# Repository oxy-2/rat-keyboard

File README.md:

# rat keyboard
i made a keyboard with a cute little screen that can show rotating text, like "i love rats <3"

so this is my hackpad aka macropad with the little hackclub program, here you can see the guide  
https://hackpad.hackclub.com/

however i have done mine with onshape instead of fusion as i have a general dislike for fusion from when i tried making pcbs with it.

so this project was done with the assistance of ai in designing and things i didn't know, obviously though i modeled out the mount  also little note the exported files are stl, step files wont export
and made the pcbs myself with kicad, and the firmware is the same as the guide, its just qmk.

as for the components they are all given by hackclub for this so i will not list a vendor or price but here  is a simple table with the components and amount needed for this project:

| Component                 | Quantity |
| ------------------------- | -------- |
| MX style switches         | 4x       |
| Seeed XIAO RP2040         | 1x       |
| 1 EC11E Rotary encoder    | 1x       |
| 0.91 inch OLED display    | 1x       |
| white blank DSA keycaps   | 4x       |
| M3x16mm screws            | 5x       |
| M3x5mx4mm heatset inserts | 5x       |

but yeah so the build will of course need its pcbs, the pcbs fit the under the max size of the hackpad guide, so it should be cheap enough as just a two layer under 100x100 mm pcb, also the case should fit, when i made the case i decided id do the pcb with some extra money from me or sum to make it white and maybe maybe maybe ENIG, but yeah thats for me to get after i make this but yeah so i wanted a pretty pcb and to show it off so the case is a mount to hold it up and its just open to air, i personally like the ig exposed style, anyways here are pictures of the pcb.

front:

back:

oh and heres a pic from cad:

shcematic:

pcb in kicad:

but yeah so its got 4 keys, a rotary encoder with a switch and a oled, on the oled it has wrapping text that spins and its correlated to the system volume which the knob can change and a press down is a volume mute and unmute, rn the text is "i love rats <3" but if you don't like it or want sum else you can easily change it in the firmware.
oh yeah btw the onshape document is set to public so you can check it out at the link [here](https://cad.onshape.com/documents/287181afc6cc633650b51987/w/7a5487d578a409bebd3abe5a/e/d938dcab35d572d75bd97ac9?renderMode=0&uiState=6aafc34289e7540c48d2f54f)
thank you for your time <3

-oxy

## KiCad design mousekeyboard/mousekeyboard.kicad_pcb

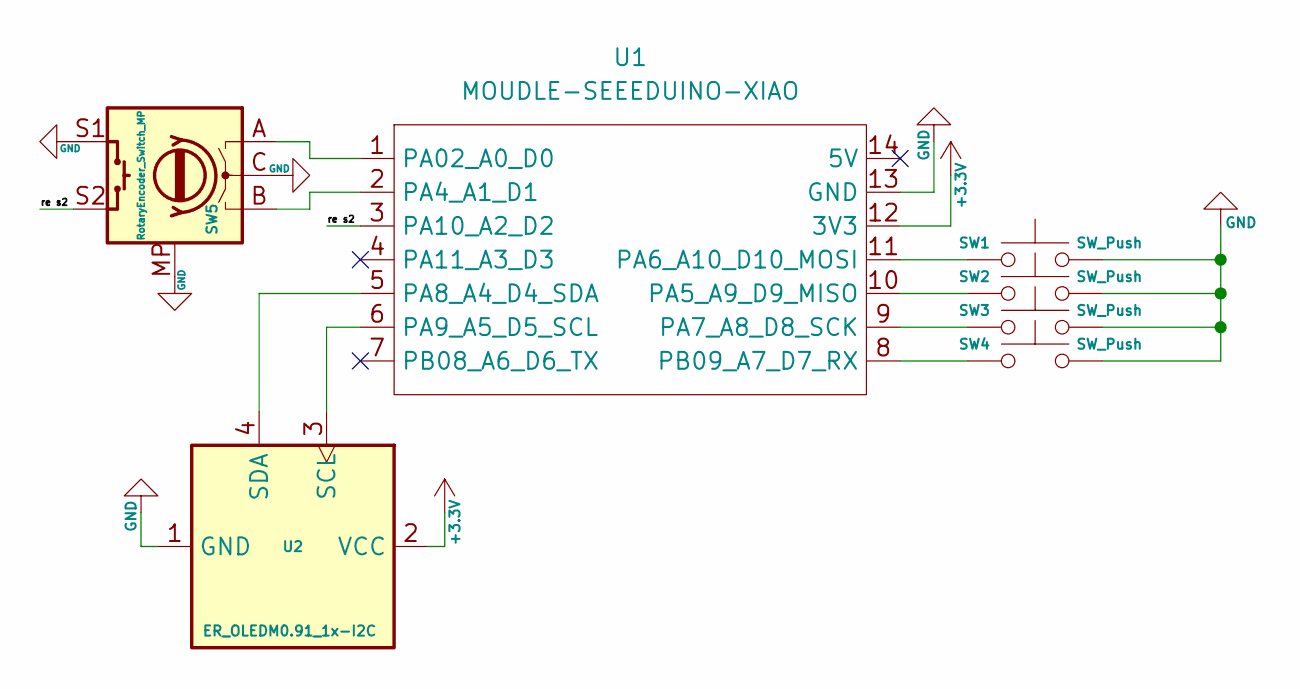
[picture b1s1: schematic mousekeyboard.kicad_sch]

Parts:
SW1, SW2, SW3, SW4: SW_Push; SW_Cherry_MX_1.00u_PCB
SW5: RotaryEncoder_Switch_MP; RotaryEncoder_Alps_EC11E-Switch_Vertical_H20mm
U1: MOUDLE-SEEEDUINO-XIAO; XIAO-Generic-Hybrid-14P-2.54-21X17.8MM
U2: ER_OLEDM0.91_1x-I2C

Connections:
+3.3V: U1.12 (3V3), U2.2 (VCC)
/re s2: SW5.S2, U1.3 (PA10_A2_D2)
GND: SW1.2, SW2.2, SW3.2, SW4.2, SW5.C, SW5.MP, SW5.S1, U1.13 (GND), U2.1 (GND)
unnamed: SW5.A, U1.1 (PA02_A0_D0)
unnamed: SW5.B, U1.2 (PA4_A1_D1)
unnamed: SW2.1, U1.10 (PA5_A9_D9_MISO)
unnamed: SW1.1, U1.11 (PA6_A10_D10_MOSI)
unnamed: SW3.1, U1.9 (PA7_A8_D8_SCK)
unnamed: U1.5 (PA8_A4_D4_SDA), U2.4 (SDA)
unnamed: U1.6 (PA9_A5_D5_SCL), U2.3 (SCL)
unnamed: SW4.1, U1.8 (PB09_A7_D7_RX)

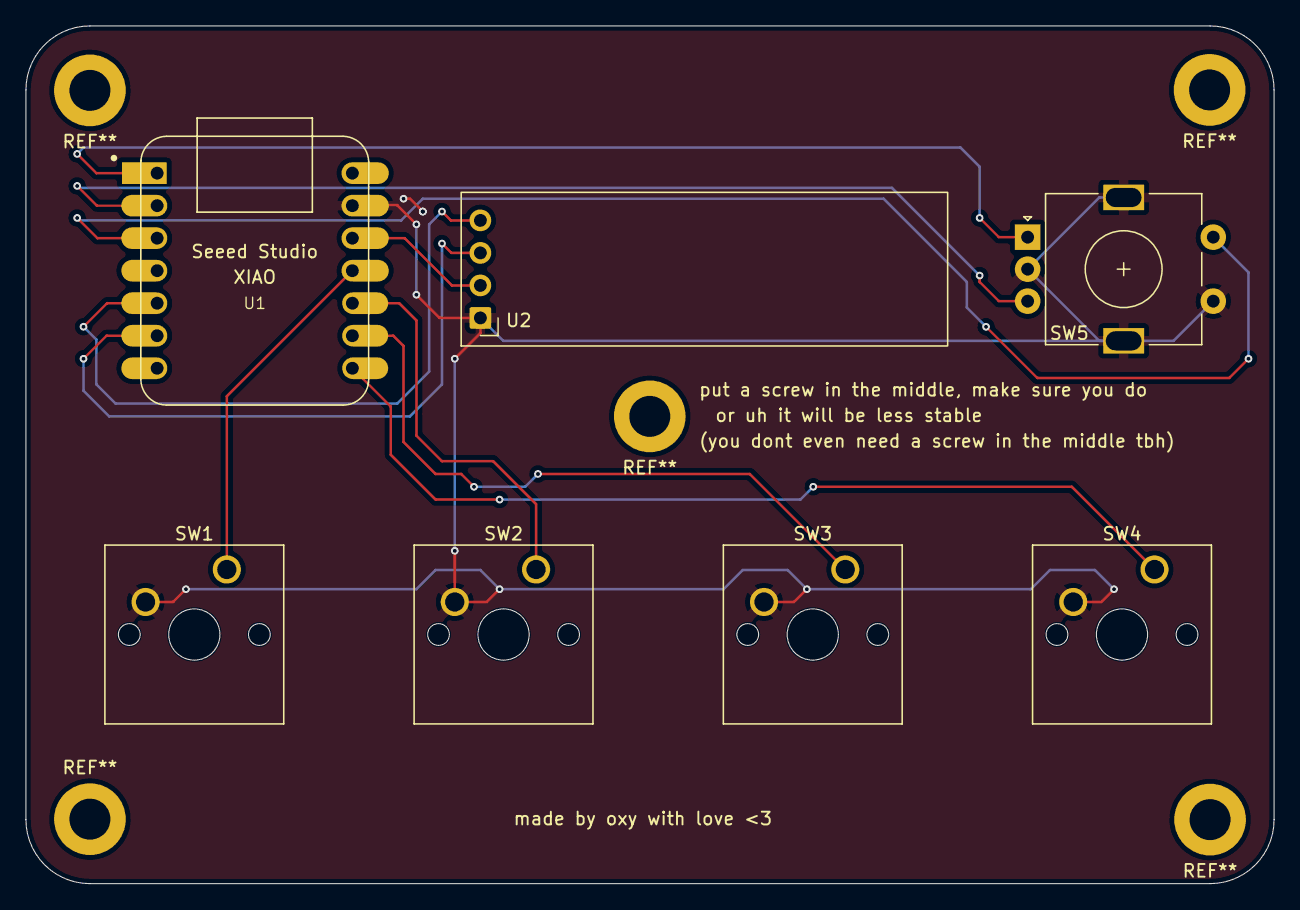
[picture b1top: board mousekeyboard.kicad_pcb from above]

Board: 2 copper layers, 97.5 x 67.0 mm, 7 parts (0 on the bottom side), 11 nets.
